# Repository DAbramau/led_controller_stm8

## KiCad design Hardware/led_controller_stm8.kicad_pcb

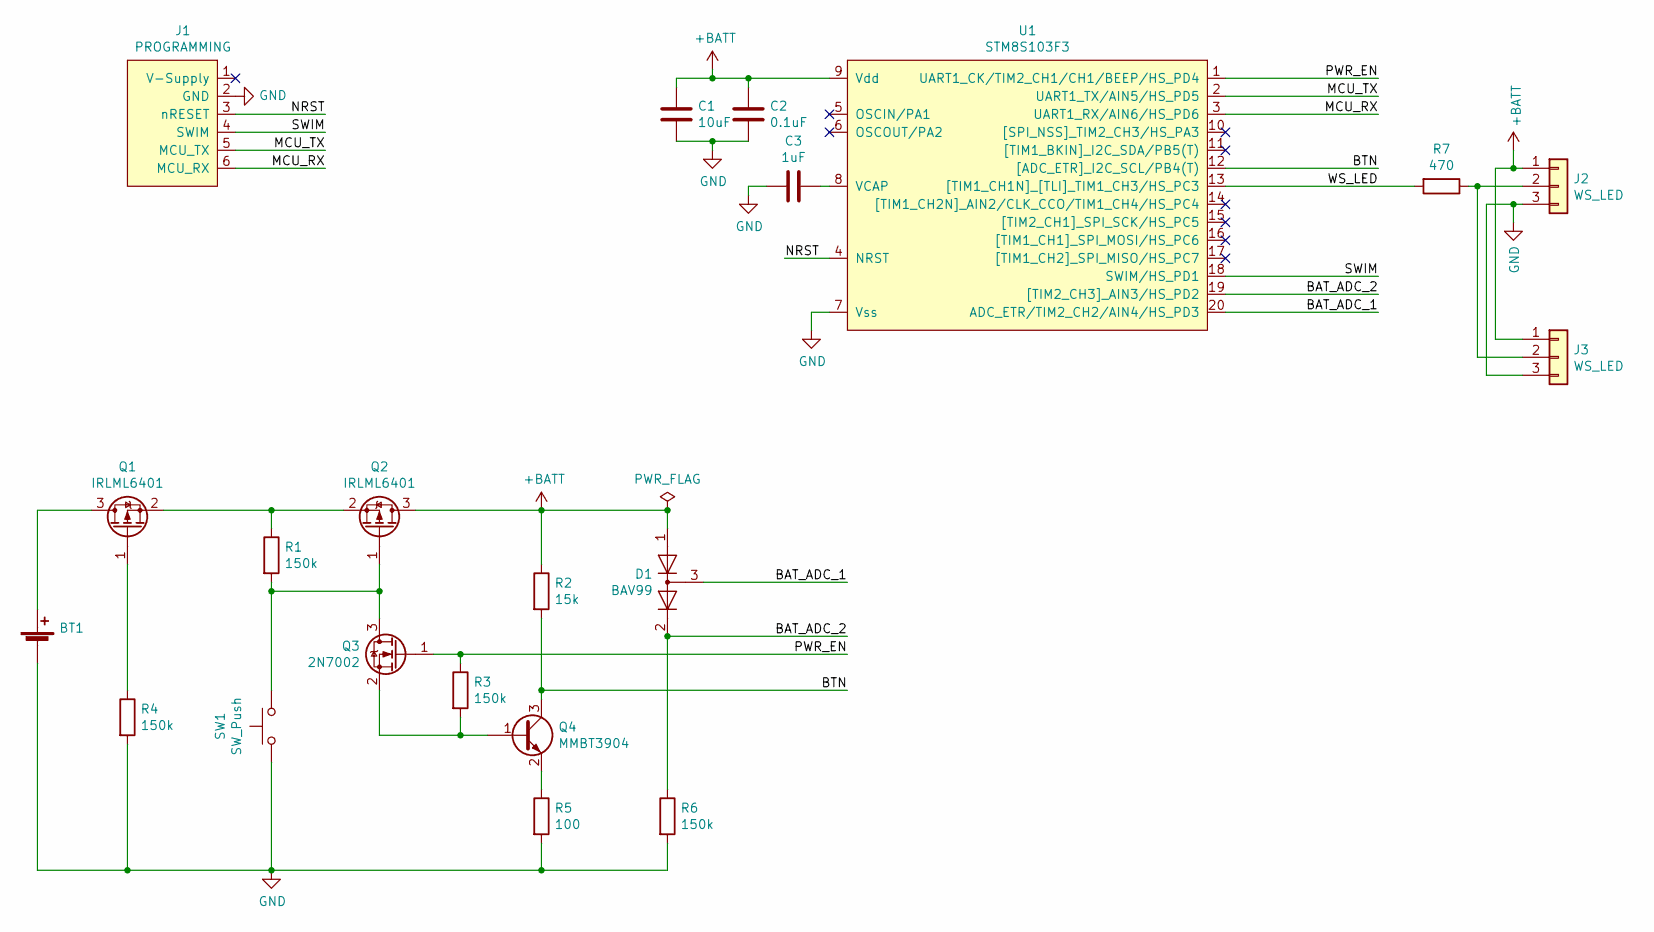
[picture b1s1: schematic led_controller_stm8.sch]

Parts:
BT1: Battery_Cell; CB_18650_PC2
C1: 10uF; C_0805_2012Metric_Pad1.15x1.40mm_HandSolder
C2: 0.1uF; C_0805_2012Metric_Pad1.15x1.40mm_HandSolder
C3: 1uF; C_0805_2012Metric_Pad1.15x1.40mm_HandSolder
D1: BAV99; SOT-23
J1: PROGRAMMING; IDC-1.27-6P
J2: WS_LED; JST_XH_S3B-XH-A-1_1x03_P2.50mm_Horizontal
J3: WS_LED; JST_XH_B3B-XH-A_1x03_P2.50mm_Vertical
Q1, Q2: IRLML6401; SOT-23
Q3: 2N7002; SOT-23
Q4: MMBT3904; SOT-23
R1, R3, R4, R6: 150k; R_0805_2012Metric_Pad1.15x1.40mm_HandSolder
R2: 15k; R_0805_2012Metric_Pad1.15x1.40mm_HandSolder
R5: 100; R_0805_2012Metric_Pad1.15x1.40mm_HandSolder
R7: 470; R_0805_2012Metric_Pad1.15x1.40mm_HandSolder
SW1: SW_Push; SW_PUSH_6mm_H13mm
U1: STM8S103F3; TSSOP-20_4.4x6.5mm_P0.65mm

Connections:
+BATT: C1.2, C2.2, D1.1 (K), J2.1, J3.1, Q2.3 (D), R2.1, U1.9 (Vdd)
/BAT_ADC_1: D1.3 (K), U1.20 (ADC_ETR/TIM2_CH2/AIN4/HS_PD3)
/BAT_ADC_2: D1.2 (A), R6.1, U1.19 ([TIM2_CH3]_AIN3/HS_PD2)
/BTN: Q4.3 (C), R2.2, U1.12 ([ADC_ETR]_I2C_SCL/PB4(T))
/MCU_RX: J1.6 (MCU_RX), U1.3 (UART1_RX/AIN6/HS_PD6)
/MCU_TX: J1.5 (MCU_TX), U1.2 (UART1_TX/AIN5/HS_PD5)
/NRST: J1.3 (nRESET), U1.4 (NRST)
/PWR_EN: Q3.1 (G), R3.1, U1.1 (UART1_CK/TIM2_CH1/CH1/BEEP/HS_PD4)
/SWIM: J1.4 (SWIM), U1.18 (SWIM/HS_PD1)
/WS_LED: R7.2, U1.13 ([TIM1_CH1N]_[TLI]_TIM1_CH3/HS_PC3)
GND: BT1.2 (-), C1.1, C2.1, C3.2, J1.2 (GND), J2.3, J3.3, R4.2, R5.2, R6.2, SW1.1, U1.7 (Vss)
unnamed: BT1.1 (+), Q1.3 (D)
unnamed: C3.1, U1.8 (VCAP)
unnamed: J2.2, J3.2, R7.1
unnamed: Q1.1 (G), R4.1
unnamed: Q1.2 (S), Q2.2 (S), R1.1
unnamed: Q2.1 (G), Q3.3 (D), R1.2, SW1.2
unnamed: Q3.2 (S), Q4.1 (B), R3.2
unnamed: Q4.2 (E), R5.1

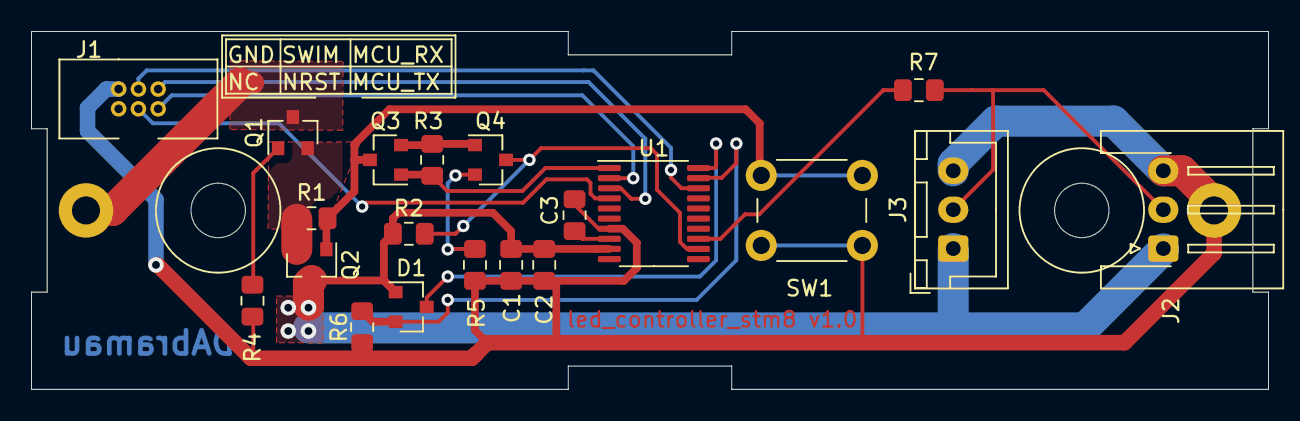
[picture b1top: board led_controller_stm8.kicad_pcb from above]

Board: 2 copper layers, 79.5 x 23.0 mm, 21 parts (1 on the bottom side), 19 nets.

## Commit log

2021-09-26 rearrange folders
2021-09-26 add kicad project
2021-09-26 add ts_init prototype
2021-09-26 add schematics and pcd
2021-09-26 update pcb
2021-09-30 add pcb
2021-10-03 add mounting holes to CB_18650_PC2; update pcb
2021-10-04 add second horizontal led connector
2021-10-04 add idc connector legend; add board name
2021-10-05 add Production version 1.0
